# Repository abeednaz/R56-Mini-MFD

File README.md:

<h1>R56 MINI Cooper Multi-Function Display</h1>

---

<h2>Project Background</h2>
The second generation of BMW MINI Cooper S is a great car, but it is missing important metrology from the factory. It has a coolant temperature sensor, but there is no gauge to view the temperature. Technically a driver can view the temperature by entering a <a href="https://youtu.be/KhFTyjIRaBU?si=EUw38T1VuMLcuM9A">secret menu</a>, but this is not practical except for debugging purposes as it requires a long series of inputs to display. The car otherwise uses the coolant temperature sensor only to flash a warning light when the engine has already overheated. 

Knowledge of engine temperature is important to me for two reasons:

- Situational awareness to know when engine is up to temperature in order to use full throttle and rev range
- Situational awareness in case of cooling system failures, such as leaking plastic thermostat housing

Aftermarket solutions such as the ScanGauge II and CravenSpeed Gauge Kit exist; however I felt that the ScanGauge did not suit the interior design style of the MINI, and the CravenSpeed kit cost cost more than I was willing to spend on an accessory. This project aimed to add an engine temperature display to the MINI that fits the MINI's interior design language and to take advantage of other sensors that the vehicle has to offer.

<h2>Project Demonstrations</h2>

<h3>Scrolling through the different available sensors</h3>

https://github.com/user-attachments/assets/e3969205-8839-4358-a2c1-934d2600cd6b

<h3>Getting engine up to operating temperature</h3>

https://github.com/user-attachments/assets/219b7ffb-3163-47f8-8801-7a190b6d4f65

<h3>Boost pressure demonstration</h3>

https://github.com/user-attachments/assets/48d6ecf0-7964-4478-b5fc-5cb366bfa986

<h2>Project Block Diagram</h2>

This project consists of the following components:
- COTS ESP32-based microcontroller with AMOLED screen
- COTS ELM327 OBD-II diagnostic code scanner
- Custom PCB to supply ELM327 and ESP32 with 5V and 12V only when vehicle ignition is switched on
- Custom PCB to provide microcontroller with button, ambient light sensor, and 5V from the power supply PCB

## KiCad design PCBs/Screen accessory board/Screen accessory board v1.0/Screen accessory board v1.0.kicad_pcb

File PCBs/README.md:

# PCB Overview

## OBD-II Connector Board
The connector board connects to the J1962 connector under the vehicle's steering column. Pinout of the vehicle's connector:

The connector board reroutes the battery power (pin 16) through a MOSFET switch triggered by the ignition signal (pin 1). The 12V switched power line is distributed to an ELM327 OBD-II code scanner, a 12V DC power connector, and a 12V--5V buck converter to power the gauge electronics. This allows the code scanner and gauge to only be switched on while the vehicle is in accesory mode or the engine is running, reducing the parasitic battery drain while the vehicle is off to ~145 nW.

### Connector board v2.7 rework:
Two components (SW1 and Q2) were captured incorrectly in the schematic and PCB. The rework instructions are as follows:
1. Remove SW1 and solder wire between P1 and P2
2. Cut trace at X1
3. Cut trace at X2
4. Solder wire between P3 and P4
5. Solder wire between P5 and P6

 PCB Front                 | PCB Back
:-------------------------:|:-------------------------:
  |  

### Assembly photos
 Soldered assembly front   | Soldered assembly back    | With connector
:-------------------------:|:-------------------------:|:--------------:|
 |   | 

## Screen Accessory Board
The screen used for this project is an off-the-shelf solution from [Waveshare](https://www.waveshare.com/wiki/ESP32-S3-Touch-AMOLED-1.75#Hardware_Description). It is a fully-contained solution with an ESP32-S3 microprocesor and a high-resolution AMOLED screen in addition to a PMIC and IMU. To adapt it for the gauge, I needed to add a button to allow a user to switch between gauges, and I needed a sensor to check the ambient light level to dim the display at night. I also needed a way to switch the gauge on and off, so I moved the switch from the OBD-II distribution board to the screen accessory board.

 PCB Front                 | PCB Back
:-------------------------:|:-------------------------:
 | 

### Assembly photos
 Soldered assembly front   | Soldered assembly back    
:-------------------------:|:-------------------------:
 |

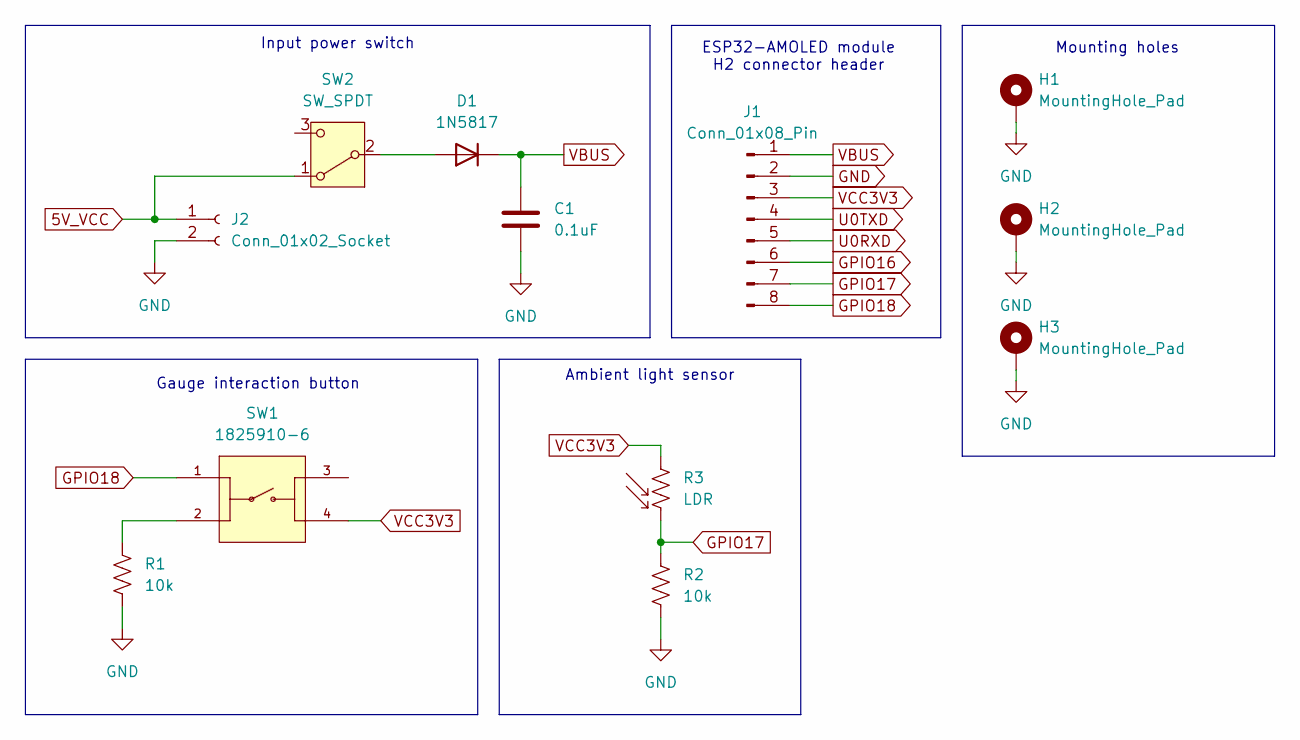
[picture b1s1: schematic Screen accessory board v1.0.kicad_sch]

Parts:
C1: 0.1uF; C_Disc_D4.3mm_W1.9mm_P5.00mm
D1: 1N5817; D_DO-15_P12.70mm_Horizontal
H1, H2, H3: MountingHole_Pad; MountingHole_2.2mm_M2_Pad
J1: Conn_01x08_Pin; PinHeader_1x08_P2.54mm_Vertical
J2: Conn_01x02_Socket; Molex_Nano-Fit_105313-xx02_1x02_P2.50mm_Horizontal
R1, R2: 10k; R_Axial_DIN0207_L6.3mm_D2.5mm_P10.16mm_Horizontal
R3: LDR; R_LDR_5.1x4.3mm_P3.4mm_Vertical_(respaced_silkscreen)
SW1: 1825910-6; SW_1825910-6-4; PARTREV C10
SW2: SW_SPDT; SW_1218_EWI

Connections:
5V_VCC: J2.1, SW2.1 (A)
GND: C1.2, H1.1, H2.1, H3.1, J1.2, J2.2, R1.1, R2.1
GPIO16: J1.6
GPIO17: J1.7, R2.2, R3.2
GPIO18: J1.8, SW1.1
unnamed: D1.2 (A), SW2.2 (B)
unnamed: R1.2, SW1.2
U0RXD: J1.5
U0TXD: J1.4
VBUS: C1.1, D1.1 (K), J1.1
VCC3V3: J1.3, R3.1, SW1.4

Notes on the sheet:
Gauge interaction button
Input power switch
ESP32-AMOLED module H2 connector header
Ambient light sensor
Mounting holes

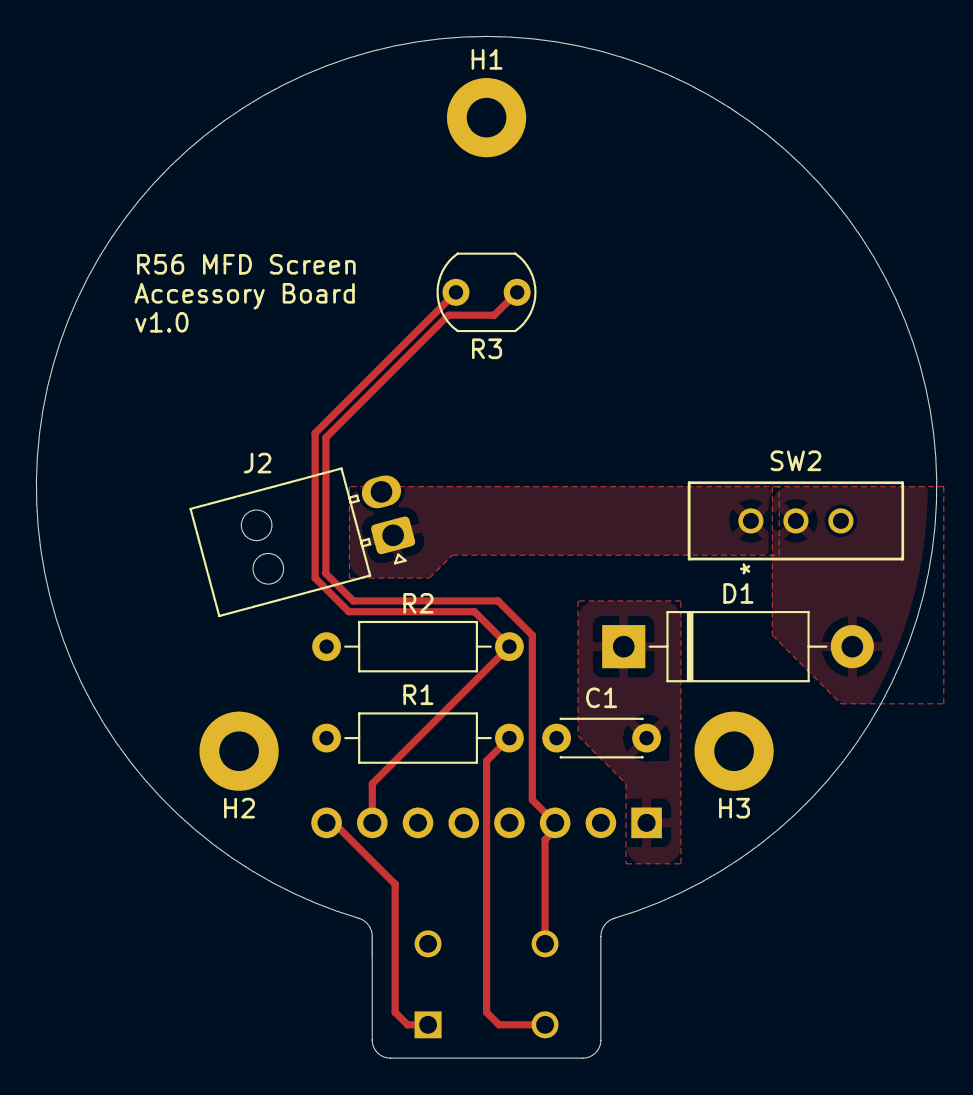
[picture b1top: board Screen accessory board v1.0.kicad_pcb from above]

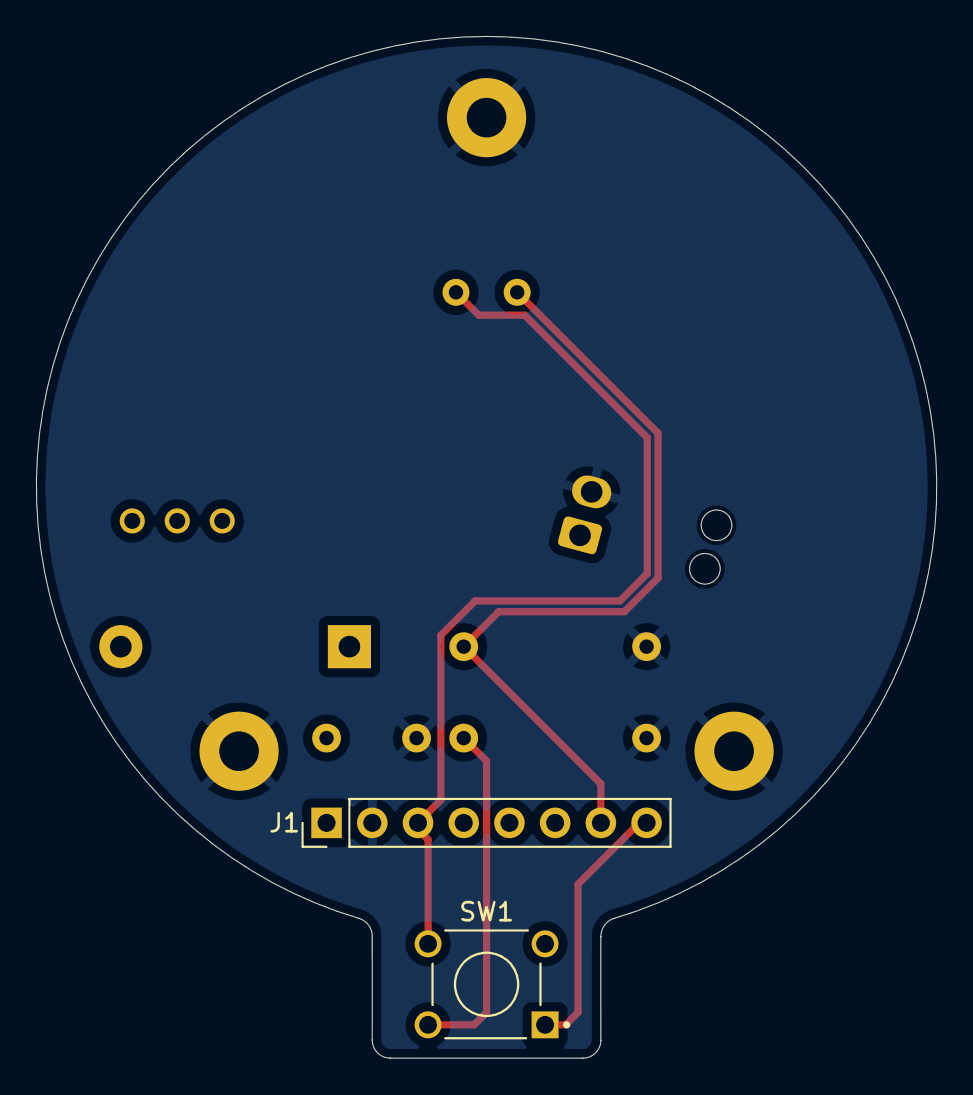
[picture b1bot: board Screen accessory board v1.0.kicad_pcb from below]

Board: 2 copper layers, 50.0 x 56.8 mm, 12 parts (2 on the bottom side), 8 nets.

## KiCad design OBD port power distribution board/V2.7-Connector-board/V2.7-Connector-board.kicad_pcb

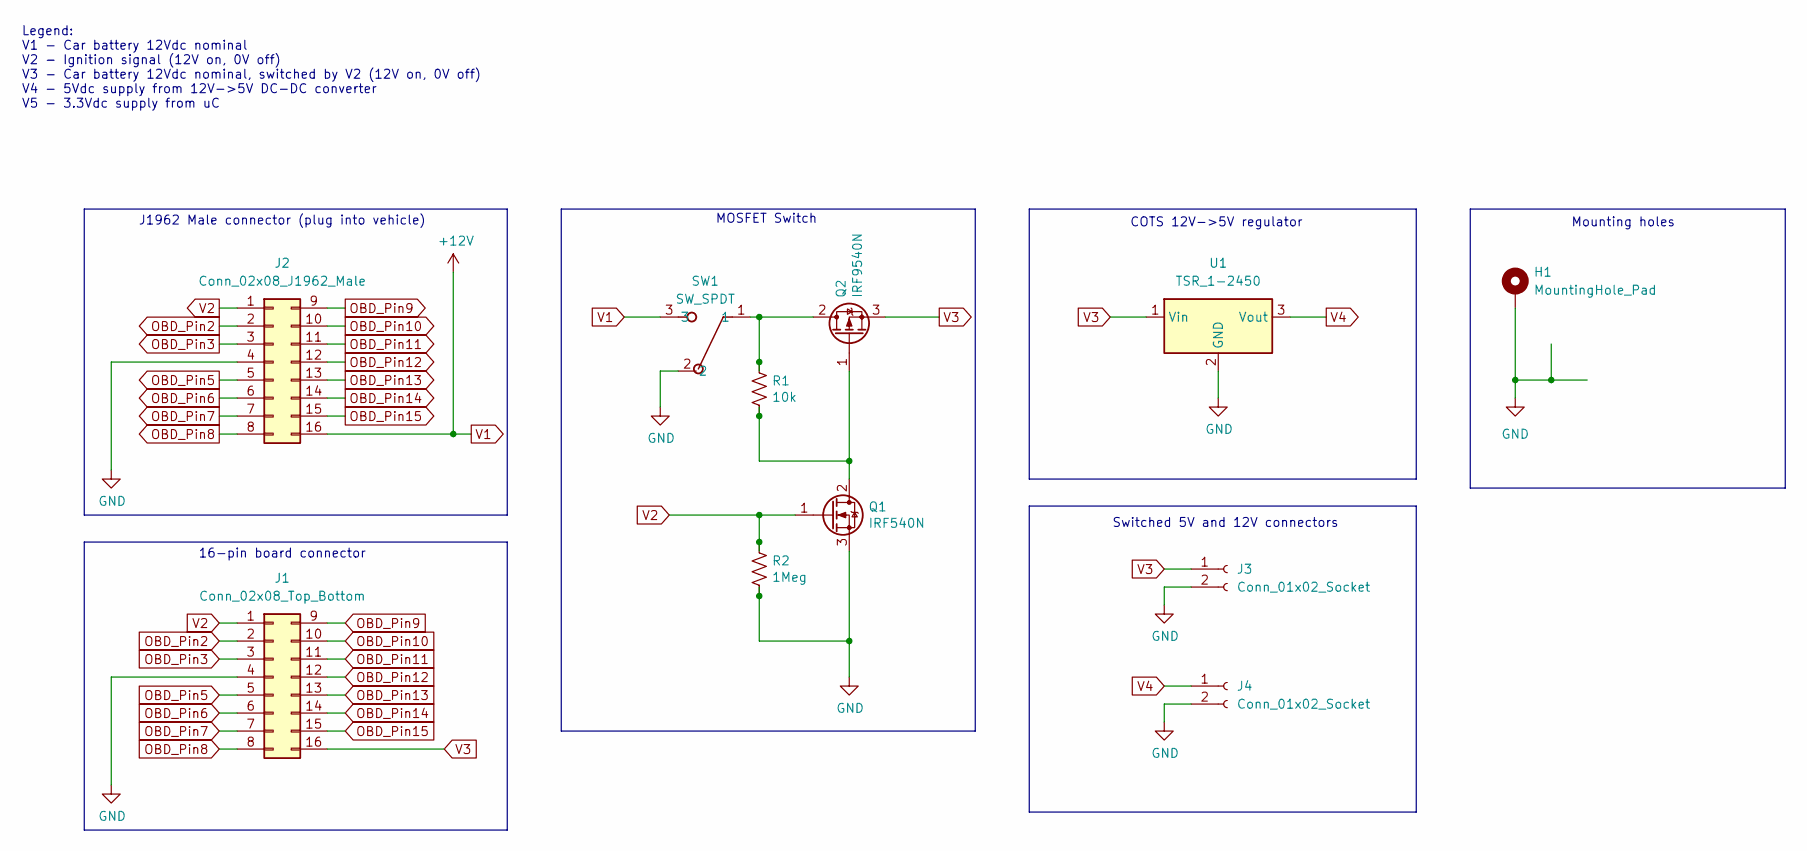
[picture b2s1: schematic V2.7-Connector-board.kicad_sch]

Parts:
H1: MountingHole_Pad; MountingHole_3.2mm_M3_Pad
J1: Conn_02x08_Top_Bottom; CONN16_5016451620_MOL_Renumbered
J2: Conn_02x08_J1962_Male; OBD-II_Male_Connector_Renumbered
J3, J4: Conn_01x02_Socket; CONN02_2125280200_MOL
Q1: IRF540N; TO-220-3_Vertical
Q2: IRF9540N; TO-220-3_Vertical
R1: 10k; R_Axial_DIN0207_L6.3mm_D2.5mm_P10.16mm_Horizontal
R2: 1Meg; R_Axial_DIN0207_L6.3mm_D2.5mm_P10.16mm_Horizontal
SW1: SW_SPDT; SW_1218_EWI
U1: TSR_1-2450; Converter_DCDC_TRACO_TSR-1_THT

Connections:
GND: H1.1, J1.4, J2.4, J3.2, J4.2, Q1.3 (S), R2.1, SW1.2, U1.2 (GND)
unnamed: Q1.2 (D), Q2.1 (G), R1.1
unnamed: Q2.2 (D), R1.2, SW1.1
OBD_Pin2: J1.2, J2.2
OBD_Pin3: J1.3, J2.3
OBD_Pin5: J1.5, J2.5
OBD_Pin6: J1.6, J2.6
OBD_Pin7: J1.7, J2.7
OBD_Pin8: J1.8, J2.8
OBD_Pin9: J1.9, J2.9
OBD_Pin10: J1.10, J2.10
OBD_Pin11: J1.11, J2.11
OBD_Pin12: J1.12, J2.12
OBD_Pin13: J1.13, J2.13
OBD_Pin14: J1.14, J2.14
OBD_Pin15: J1.15, J2.15
V1: J2.16, SW1.3
V2: J1.1, J2.1, Q1.1 (G), R2.2
V3: J1.16, J3.1, Q2.3 (S), U1.1 (Vin)
V4: J4.1, U1.3 (Vout)

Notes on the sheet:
COTS 12V->5V regulator
MOSFET Switch
Switched 5V and 12V connectors
J1962 Male connector (plug into vehicle)
Legend: V1 - Car battery 12Vdc nominal V2 - Ignition signal (12V on, 0V off) V3 - Car battery 12Vdc nominal, switched by V2 (12V on, 0V off) V4 - 5Vdc supply from 12V->5V DC-DC converter V5 - 3.3Vdc supply from uC
Mounting holes
16-pin board connector

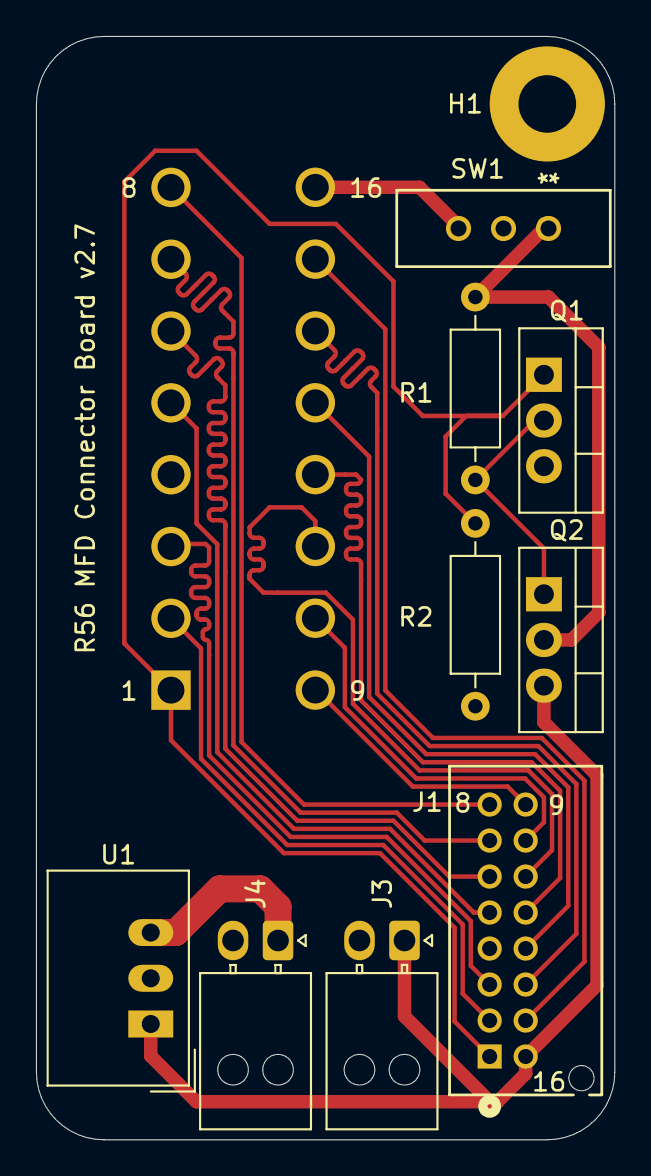
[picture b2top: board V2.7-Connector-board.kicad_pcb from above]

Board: 2 copper layers, 32.1 x 61.3 mm, 11 parts (1 on the bottom side), 20 nets.

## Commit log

2024-03-11 first commit--adding all test programs
2024-03-11 reorganized test programs
2024-03-17 added new gauge painter library
2024-03-24 new image files, added more functions to Gauge library
2024-03-30 updated referenced images with numbers, updated gauge to display numbers
2024-08-14 added gauge icons and conversion script
2024-08-14 updated RGB565_combiner and icons
2024-08-14 added test of gauge with Adafruit GFX library
2024-08-14 new bitmaps confirmed to work in test sketch
2024-08-15 new gauge library WIP to work with the GFX library
2024-08-16 updated gauge painter library to print numbers only as needed (does not print a number that hasn't changed since the last print to reduce flickering effect)
2024-08-20 updated gauge painter with more efficient index painting (only prints indices different from last gauge state)
2025-06-01 begin writing main program which polls OBD-II parameters live
2025-06-05 updated main program to use button and screen
2025-06-16 added new test file which writes a CSV of processed PID data to serial port for validation of PID conversions (use CoolTerm to log)
2025-08-10 Begin testing with WaveShare ESP32 AMOLED module. Have test program with 1 index being toggled on and off
2025-08-10 Updated gauge test with all gauge indices, using transformation/repetition of one index
2025-08-10 Updated screen test to use individual images for each index for improved visual update speed
2025-08-11 added custom font and number printing
2025-08-17 Started LVGL based screen library
2025-08-17 LVGL screen library able to fill bg
2025-09-09 added index printing fn which only draws as needed
2025-09-10 added sensor icon display (WIP w/ hardcoded vars)
2025-09-10 Added connector board PCB
2025-09-13 UI is functional for inputs of coolant temp, oil temp, oil pressure, fuel pressure, boost pressure
2025-09-14 WIP use of SD card to free program storage space (was at 82% usage when using .c files to store bitmaps)
2025-09-14 Using SD card for drawing of gauge indices, down to 62% progmem usage
2025-09-16 Removed dependencies to icon .c files. 51% program storage space used
2025-09-20 Created LVGL filesystem driver to incorporate fonts onto SD card
2025-09-28 transfered display driver functions from Gauge.cpp to separate display driver files; added SD card file structure for reference
2025-09-28 general code cleanup
2025-09-28 changed MFD_Main to use new AMOLED gauge library. Having an issue where program crashes on processPID()
2025-09-30 working program for full MFD; Have correct temperature displays
2025-10-05 add ambient light sensor support for brightness setting (ADC via GPIO pin 17)
2025-10-15 Re-organize MFD repository
2025-10-15 added CAD for connector board housing, pictures
2025-10-15 Add MOSFET switch sim
2025-12-27 Added new test/logging program for OBD-II extended service (0x22) addressing
2025-12-29 WIP modifying MFD program to include 0x22 PIDs and code improvements
2025-12-29 Rewrite of state machine logic to make adding future PIDs more modular, corrections to processing of pressure PIDs using service 22
2026-01-11 Add new logs, logging program changes, CAD for screen assembly
2026-01-11 add placeholder image for readme
2026-01-12 add readme image
2026-01-12 Add partial BOM, update READMEs
2026-02-05 WIP trip computer screen, added capability to switch between two GUIs
2026-02-05 WIP trip computer screen: added new font, access method for trip computer screen, placeholder text
